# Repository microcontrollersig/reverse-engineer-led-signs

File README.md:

# Figuring out how a commerical Led signs work

#### Images
https://github.com/microcontrollersig/reverse-engineer-led-signs/blob/master/images/readme.md

#### LED matrix(5 columns, 7rows, 14-pins)
http://www.kingbrightusa.com/images/catalog/SPEC/TA20-11EWA.pdf

#### 74HC245
http://www.mouser.com/ds/2/149/MM74HC245A-71310.pdf
http://www.ti.com/lit/ds/symlink/sn74hc245.pdf

#### 74HC373
http://www.st.com/content/ccc/resource/technical/document/datasheet/group1/96/71/e4/bd/17/76/4e/c7/CD00000305/files/CD00000305.pdf/jcr:content/translations/en.CD00000305.pdf
http://www.ti.com/lit/ds/symlink/cd74hc373.pdf

#### ULN2003A
https://www.onsemi.com/pub/Collateral/MC1413-D.PDF
http://www.tij.co.jp/jp/lit/ds/slrs027o/slrs027o.pdf

#### 74HC237B
http://www.ti.com/lit/ds/symlink/cd74hc237.pdf

# Files in Repository
Main one is **ledmatrixmodule.fzz** . You need to install **Fritzing** to view it (schematic view). If you can't be stuffed, open **ledmatrixmodule_schem.pdf**

# Things Learned
1. Rows in the first half of the board are connected, rows in the second half are connected,
   but rows in first half are not connected to the second.
2. Rows get their data from output of 3-8 demux (74HC237), the three inputs of demux are connected to input connector
3. Columns get their data from the latches (74HC373), inputs of which are connected to input connector.
4. Row scanning occurs, the darlington array (ULN2003) inverts its inputs, result being that one line will be LOW, the rest HIGH
   at any point.
5. There are 2 ULN2003A. Output of 1 ULN2003A connected to the rows in the first half,
   the other ULN2003A connected to rows in second half.
6. Corresponding inputs of both ULN2003A are connected.

# Interesting Pictures

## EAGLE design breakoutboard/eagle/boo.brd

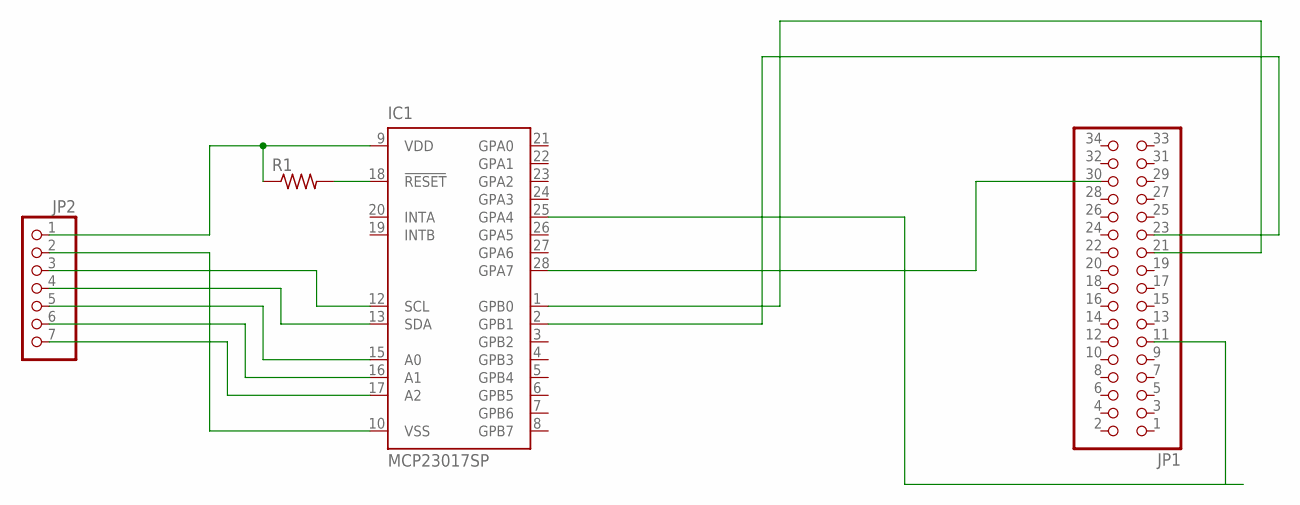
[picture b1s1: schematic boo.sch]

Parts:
IC1: MCP23017SP; DIL28-3
JP1: PINHD-2X17; 2X17
JP2: PINHD-1X7; 1X07
R1: R-US_0207/10; 0207/10

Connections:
unnamed: IC1.1 (GPB0), JP1.21
unnamed: IC1.2 (GPB1), JP1.23
unnamed: IC1.9 (VDD), JP2.1, R1.1
unnamed: IC1.10 (VSS), JP2.2
unnamed: IC1.12 (SCL), JP2.3
unnamed: IC1.13 (SDA), JP2.4
unnamed: IC1.15 (A0), JP2.5
unnamed: IC1.17 (A2), JP2.7
unnamed: IC1.18 (!RESET), R1.2
unnamed: IC1.28 (GPA7), JP1.30
unnamed: IC1.25 (GPA4), JP1.11

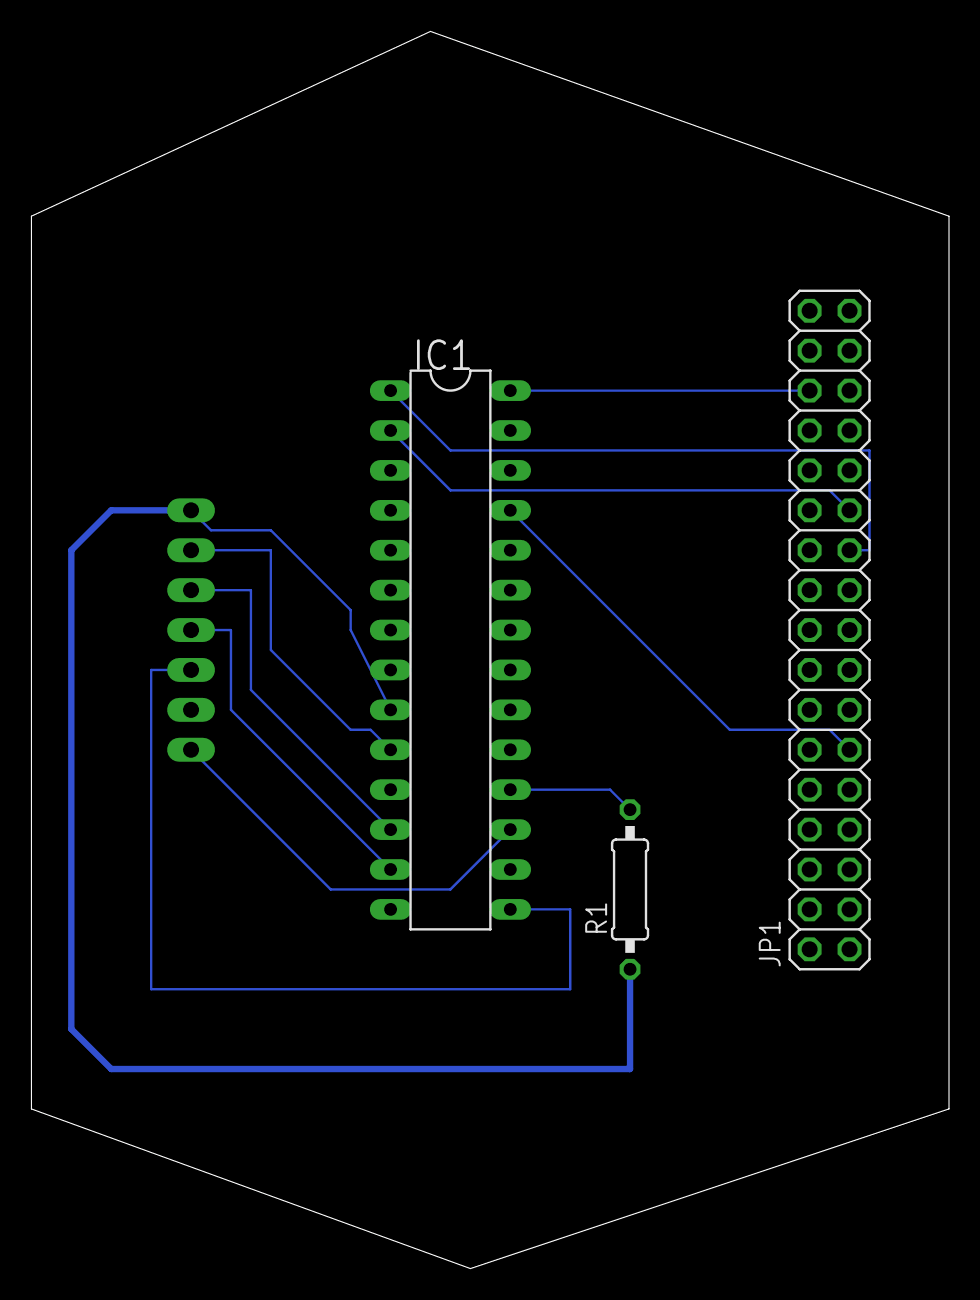
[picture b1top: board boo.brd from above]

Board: 2 copper layers, 58.4 x 78.7 mm, 4 parts (1 on the bottom side), 11 nets.

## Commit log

2017-10-22 Rename eepromseansign.lst to eepromseansignlst.asm
